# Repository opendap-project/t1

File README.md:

# t1

| Folder | Content |
| --- | --- |
| [`board/`](board/README.md) | Main board of the OpenDAP T1: the SoC-based single board computer, its auxiliary MCUs and simulations |
| [`case/`](case/README.md) | The physical case of the OpenDAP T1: the core with its basic back cover, the device-side HAT case mechanics, and the mount that faceplates attach to |
| [`faceplates/cassette/`](faceplates/cassette/README.md) | Cassette faceplate, inspired by cassette Walkmans |
| [`faceplates/classic/`](faceplates/classic/README.md) | Classic faceplate, inspired by classic portable music players |
| [`faceplates/touch/`](faceplates/touch/README.md) | Touch faceplate, the default faceplate: touch display, status LED, microphone |
| [`product/`](product/README.md) | Product integration of the OpenDAP T1: product requirements, the complete assembly and system simulations, built from the exports of every component |

Each folder keeps its own `README.md`, `CLAUDE.md` and `REUSE.toml`; the licence texts are in `LICENSES/`. The folders came from the former `board`, `case`, `faceplate-cassette`, `faceplate-classic`, `faceplate-touch` and `t1` repositories with their history ([RFC 0017](https://github.com/opendap-project/rfcs/blob/main/text/0017-naming-and-topology.md)).

## License

This repository follows the [REUSE](https://reuse.software) layout: licence texts in `LICENSES/`, and each folder's `REUSE.toml` maps its paths. Copyright © 2026 The OpenDAP Project.

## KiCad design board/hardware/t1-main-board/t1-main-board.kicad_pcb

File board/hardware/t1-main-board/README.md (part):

# T1 main board project

The KiCad 10 project of the T1 main board. The schematic is captured block by block ([feature-block catalog](../../docs/specs/feature-blocks.md), [RFC 0011](https://github.com/opendap-project/rfcs/blob/main/text/0011-feature-blocks-and-variants.md)); the board is at its placement stage: every part placed, nothing routed ([placement v1](../../docs/specs/placement-v1.md)). Prototype 1 targets quality level Q1 ([RFC 0010](https://github.com/opendap-project/rfcs/blob/main/text/0010-quality-levels.md)).

The schematic is generated: `generator/` writes every sheet, the project file, the library tables and the project-local library parts from the board's data. Edit the generator and run it again; never edit a generated file by hand. A rerun with no change in its inputs writes byte-identical files (every UUID is derived from a stable key).

## Layout

| Path | What it is |
|---|---|
| `t1-main-board.kicad_pro` | The project: drawing sheet, text variables, ERC severities (CRAFT-158), net classes and their patterns. Generated |
| `t1-main-board.kicad_sch` | The root sheet: the block diagram. Generated |
| `power.kicad_sch`, `interconnect.kicad_sch` | The power and interconnect overviews. Generated |
| `<block>.kicad_sch` | One sheet per feature block, named after its ID without `blk.` (CRAFT-82). Generated |
| `sym-lib-table`, `fp-lib-table` | Library tables: libs `kicad/` through `${KIPRJMOD}/../lib/opendap`, the project library through `${KIPRJMOD}/../lib`, KiCad's stock libraries through `${KICAD10_SYMBOL_DIR}` and `${KICAD10_FOOTPRINT_DIR}`. Generated |
| `t1-main-board.kicad_pcb` | The board: outline, holes, stackup v3, rule areas, fiducials and every part placed; not routed. Generated by `pcb/` |
| `t1-main-board.dru.toml`, `t1-main-board.kicad_dru` | The rule sources and the composed rules ([`../rules/`](../rules/)) |
| `shields.toml` | The shield-can frames (`blk.shields`): the inside area of each frame, land, keep-outs, lid and height; the generator draws the frame lands from it and the placement reserves them (both through `pcb/shields.py`). By hand |
| `t1-main-board.craft.toml` | The craft check configuration: target level and mirrored blocks (CRAFT-34) by hand; its `[schematic]` table (rails and each block's interface, CRAFT-85, -112) generated below the marker line |
| `generator/` | The generator (Python 3.11 or later, no other dependency); `parts.area_swap` applies the area swaps of BOM v1.16 and v1.17 to every placed part |
| `pcb/` | The placement tool (Python 3.11 or later and KiCad 10's Python): `build.py` writes the board from the schematic; `plan.py` holds the placement plan and its decisions; `proximity.py` checks that every converter's and IC's capacitors stand within a bound of the pins they serve (the build fails otherwise, placement v1 decision 14); `shields.py` derives the shield frames from `../shields.toml`; `fabref.py` centres each fabrication reference in its courtyard and sizes it to fit (the writer stops on an overlap); `plan.model_for` gives the KiCad stock lands whose KiCad 10 library ships no model (Littelfuse NANO2, TI DPY0002A, SOT-523, the XxL4020 land by part height) a libs `kicad/` envelope model; `variants.py` copies the schematic's KiCad 10 design-variant data onto the footprints (the `production` population for `--variant` fab outputs); `placement-result.json` is its report (area budget, occupancy, checks, capacitor proximity, shield frames, DRC summary). Tests: `python3 -m unittest discover hardware/t1-main-board/pcb/tests`; `tests/kicad_transform_check.py` (KiCad's Python) checks the footprint transform against pcbnew |
| `../lib/symbols/T1_Main_Board.kicad_sym`, `../lib/footprints/T1_Main_Board.pretty/` | Project-only parts libs `kicad/` does not carry yet: the TPS7A1006PDSER and shield-frame symbols, the Murata DFE252012F, DFE201610E, Abracon AOTA-B201610, Coilcraft XFL3012, C&K PTS815 and Vishay WSL (doc 30100 pad table, by model and resistance range) lands, the 0.8 mm test pad (PCB-D-06) and the shield-frame lands. Generated; each land carries its libs `kicad/` envelope model (libs v0.3.3) |

## Blocks captured

Drawn from 2026-10-25. Every sheet carries the block's notes (function, absent state, constraint IDs, ADRs), an interface table and a rail table.

| Page | Sheet | Block | Content |
|---|---|---|---|
| 1 | `t1-main-board.kicad_sch` | root | Block diagram in reading rows; the LPDDR4X and eMMC buses wired pin for pin |
| 2 | `power.kicad_sch` | power | Rail table of the drawn blocks and the power tree (power tree v0.11) |
| 3 | `interconnect.kicad_sch` | interconnect | Connector list; pin maps come with the connector blocks |
| 4-7 | `charger*.kicad_sch` | `blk.charger`, `-input`, `-core`, `-battery` | TPS2121 input mux and OV interlocks; BQ25798 2S charger; CSD17575Q3 ship FET, 5 A fuse, BATP and the six battery contacts with ESD (board ADRs 0014, 0020) |
| 8 | `gauge.kicad_sch` | `blk.gauge` | BQ28Z610-R1 on the pack side, 3 mΩ low-side sense, board NTC (board ADR 0017) |
| 9 | `pwr-vsys-lv.kicad_sch` | `blk.pwr-vsys-lv` | TPS62136, VSYS to VSYS_LV 3.8 V |
| 10 | `pwr-3v3-sys.kicad_sch` | `blk.pwr-3v3-sys` | TPS62827, vcc3v3_sys 3.3 V |
| 11 | `pmic.kicad_sch` | `blk.pmic` | RK809-5: bucks, LDOs, RTC, control |
| 12 | `vdd-cpu.kicad_sch` | `blk.vdd-cpu` | TPS62870Z4 vdd_cpu with differential sense and compensation (board ADR 0026) |
| 13-20 | `soc*.kicad_sch` | `blk.soc`, `blk.soc-*` | RK3566 by IO domain: PMU IO with clock, reset and pull-ups; DDR; VCCIO1-4; VCCIO5-7; the PHYs (USB 2.0 and 3, multi-PHY, CSI RX, DSI, HDMI, eDP); supplies; ground |
| 21 | `lpddr4x.kicad_sch` | `blk.lpddr4x` | Micron MT53E1G32D2FW-046 (board ADR 0022), TPS7A1006 VDDQ, links |
| 22-33 | `audio*.kicad_sch`, `mclk`, `dac-*`, `hpa-*` | `blk.audio` and its sub-sheets | DAC supplies, divided master clocks (ADR 0019), two CS43198, ±7 V and ±6 V rails, six OPA1622 |
| 34 | `jack-se.kicad_sch` | `blk.jack-se` | The 3.5 mm jack |
| 35-37 | `rp2354*.kicad_sch` | `blk.rp2354`, `-core`, `-power` | RP2354A (one reference, three units): system and GPIO units with the 12 MHz oscillator, BOOTSEL N-FET, 27 Ω USB series, the five I2S/DSD tap positions and test pads; the supply unit with its 3.3 µH core regulator, RP_3V3 and RP_IOVDD_1V8 switches, links #21 and #30 |
| 38 | `emmc.kicad_sch` | `blk.emmc` | Samsung KLMBG2JETD-B041 eMMC, 16 GB alternate |
| 39 | `mic-ambient.kicad_sch` | `blk.mic-ambient` | IM73D122 on PDM CLK1 and SDI1, 22 Ω clock series, link #35 from MIC_1V8 |
| 40 | `jack-bal.kicad_sch` | `blk.jack-bal` | The 4.4 mm jack |
| 41 | `maskrom.kicad_sch` | `blk.maskrom` | TPS3808G01 boot window (WINDOW_N), SN74LVC1G57 and SN74LVC1G58 on vcca1v8_pmu, BAT54 from PWRON_N, DMG1012T pulling EMMC_D0 through 1 kΩ |
| 42 | `current-monitors.kicad_sch` | `blk.current-monitors` | Five INA236 on I2C1 (0x40, 0x41, 0x43; INA236B at 0x48, 0x49) and their shunts on Vishay's WSL lands: VSYS 10 mΩ, audio VSYS_LV and VSYS sides 20 mΩ each, display 100 mΩ, HAT 20 mΩ |
| 43 | `debug.kicad_sch` | `blk.debug` | Debug UART2 and I2S/DSD pads with ground, reset and PMIC pads, the spare SoC GPIO pads (the `DEBUG` bus), a pad on every rail no other sheet probes |
| 44 | `pwr-5v1.kicad_sch` | `blk.pwr-5v1` | TPS62903 5.1 V source, enabled by either port (OR of HAT5V_EN, USB_SRC_ON) |
| 45 | `usb-vbus-out.kicad_sch` | `blk.usb-vbus-out` | eFuse #D (shared limiter) and eFuse #C (USB-C source), TPS259470A (RFC 0015) |
| 46 | `usb-c.kicad_sch` | `blk.usb-c` | USB4105 receptacle, TVS2200, TPD8S300A, TPD4E05U06, FUSB302B, VBUSDET divider |
| 47 | `hat-signals.kicad_sch` | `blk.hat-signals` | DF40C-50DS flat-cable receptacle (interface v2 §9.2), USB 3 TX AC coupling |
| 48 | `hat-5v.kicad_sch` | `blk.hat-5v` | eFuse #A, FUSB302B01 (USB PD on the HAT port), VBUS discharge (RFC 0014) |
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
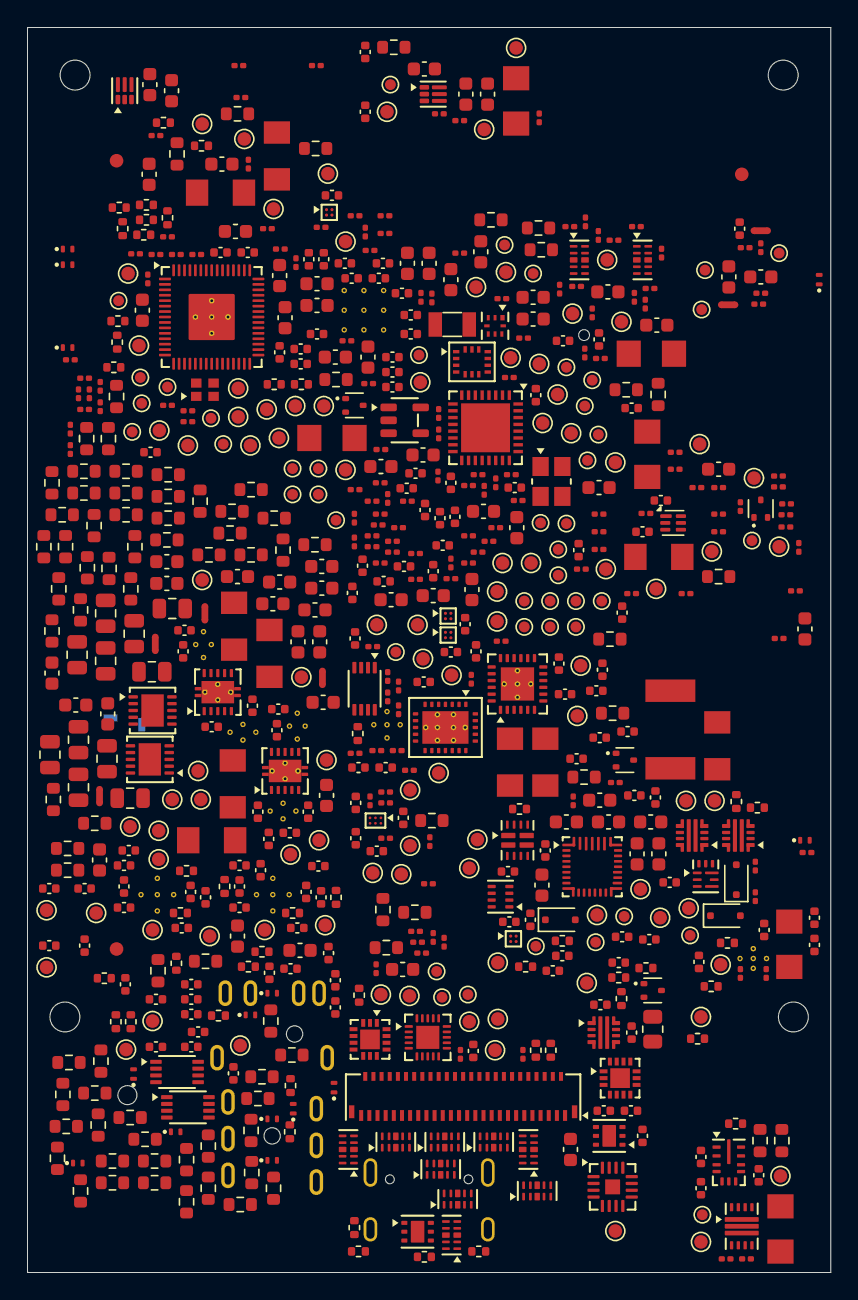
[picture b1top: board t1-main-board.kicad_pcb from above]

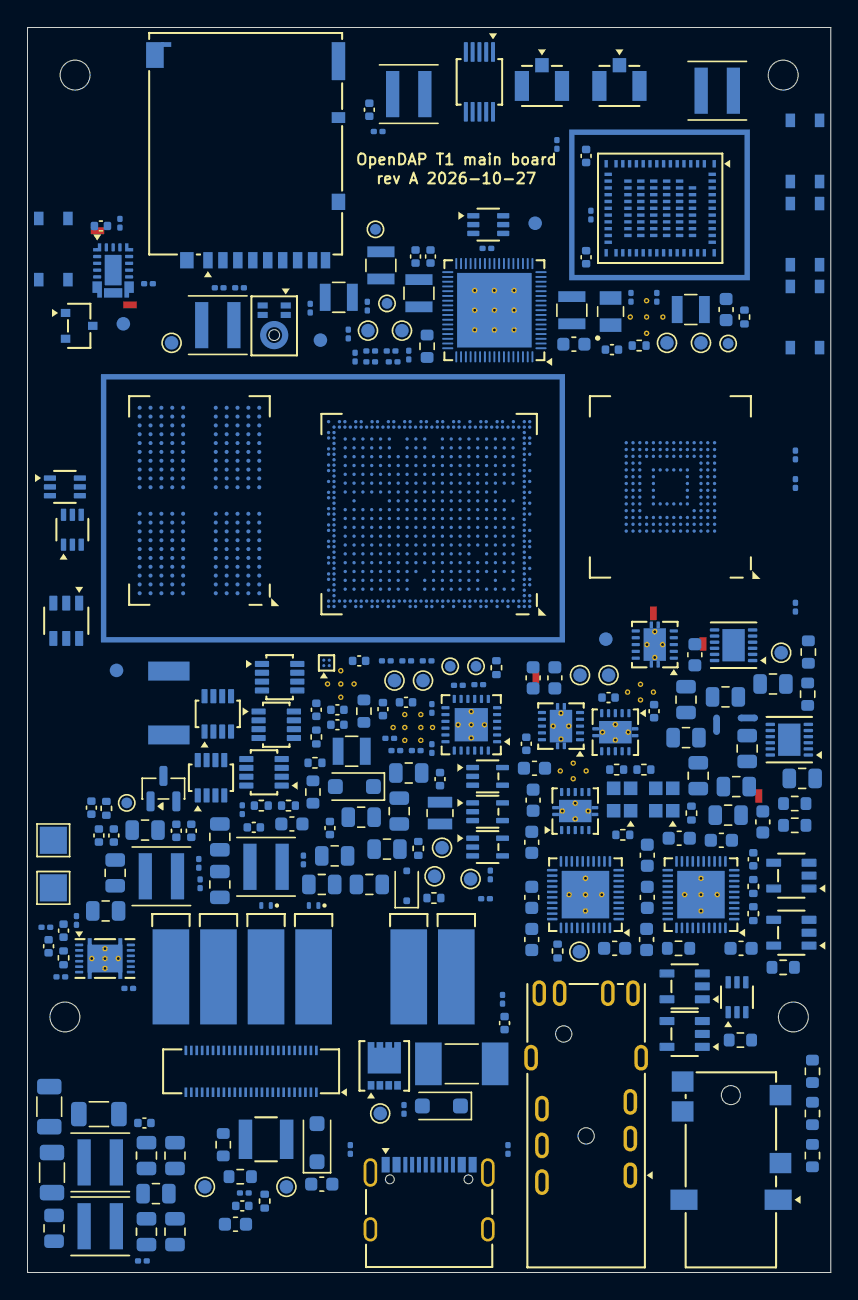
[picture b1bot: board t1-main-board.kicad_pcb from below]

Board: 6 copper layers, 59.1 x 91.6 mm, 1008 parts (279 on the bottom side), 600 nets, no tracks yet.

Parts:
A5901: Shield_Frame_SOC; Shield_Frame_SOC_34.15x19.75mm
A5902: Shield_Frame_RADIO; Shield_Frame_RADIO_13.3x11.1mm
C501, C607, C611, C617, C801, C804, C805, C806, C2401, C2408, C2409, C2503, C2504, C2506, C2603, C2604, C2606, C2804, C2812, C3005, C3006, C3011, C3012, C3205, C3206, C3211, C3212, C3305, C3306, C3311, C3312, C3902, C4201, C4202, C4203, C4204, C4205, C4805, C5502: 100 nF; C_0402_1005Metric
C502, C503, C802, C1110, C1111, C1112, C1113, C1122, C1123, C1124, C1125, C1126, C1127, C1128, C1129, C1130, C1131, C1132, C1133, C1134, C1135, C1335, C1337, C2111, C2301, C2302, C2813, C3516, C3517, C3901, C4501, C4502, C4503, C4504, C4602, C4603, C4801, C4802, C4804, C5103, C5301, C5302, C5303, C5701, C6001, C6002, C6501, C6601, C6602, C6801, C6802: 1 µF; C_0402_1005Metric
C601, C1001, C2507, C2607, C5401: 4.7 µF; C_0603_1608Metric
C602, C603, C604: 47 nF; C_0402_1005Metric
C605, C606, C612, C613, C614, C615, C616, C1004, C1101, C1103, C1106, C1108, C1116, C1117, C1118, C1119, C1120, C1121, C1328, C5001, C5002, C5003, C5104, C5501, C6201: 10 µF; C_0603_1608Metric
C608, C609, C610, C618, C619, C2814, C2815: 10 µF; C_0805_2012Metric
C803, C2402, C2403, C2404, C2405, C2501, C2502, C2505, C2508, C2510, C2512, C2513, C2514, C2515, C2516, C2601, C2602, C2605, C2608, C2610, C2612, C2613, C2614, C2615, C2616, C3801: 2.2 µF; C_0402_1005Metric
C901, C903, C904, C2902, C2903, C2904, C2906, C2907, C2908, C2911, C2912, C2913, C2914, C2915, C2916, C2917, C2918, C2919, C2920, C2921, C2922, C4402, C4403, C4404: 22 µF; C_0805_2012Metric
C902: 3.3 nF; C_0402_1005Metric
C1002, C5106: 120 pF; C_0402_1005Metric
C1003, C1102, C1104, C1105, C1107, C1109, C1208, C1311, C1312, C1313, C1318, C1321, C1323, C2112, C2113, C5105: 22 µF; C_0603_1608Metric
C1114, C1115, C1202, C1204, C1205, C1303, C1308, C1314, C1319, C1322, C1324, C1325, C1326, C1329, C1330, C1331, C1334, C1336, C1338, C1339, C1340, C1341, C1342, C1343, C1344, C1345, C1346, C1347, C1348, C1349, C2101, C2102, C2103, C2104, C2105, C2106, C2107, C2108, C2109, C2110, C2115, C3501, C3502, C3503, C3504, C3505, C3506, C3507, C3509, C3510, C3511, C3513, C3514, C4101, C4103, C4104, C4604, C4701, C4702, C5004, C5101, C5102, C5601, C5702, C5703, C5704, C6202, C6301, C6302, C6401, C6701, C6702: 100 nF; C_0201_0603Metric
C1201, C1203: 47 µF; C_0603_1608Metric
C1206: 5.6 nF; C_0402_1005Metric
C1207, C2811: 22 pF; C_0402_1005Metric
C1301, C1302: 10 pF; C_0402_1005Metric
C1304, C1305, C1306, C1307, C4505, C4803: 1 nF; C_0402_1005Metric
C1309, C1310, C1315, C1316, C1317, C1320, C1327, C1332, C1333, C2114, C2116, C2303, C2805, C2806, C3508, C3512, C3515: 4.7 µF; C_0402_1005Metric
C2304: 10 µF; C_0402_1005Metric
C2406, C2407, C2802, C4401: 10 nF; C_0402_1005Metric
C2509, C2511, C2609, C2611: 15 µF; C_0603_1608Metric
C2801: 15 pF; C_0402_1005Metric
C2803, C5402: 220 nF; C_0402_1005Metric
C2807, C2808, C2809, C2810, C2816, C2901, C2905: 4.7 µF; C_0805_2012Metric
C2817, C2818, C2819: 22 µF; C_1206_3216Metric
C2909, C2910, C2923, C2924: 470 nF; C_0603_1608Metric
C3001, C3002, C3003, C3004, C3007, C3008, C3009, C3010, C3201, C3202, C3203, C3204, C3207, C3208, C3209, C3210, C3301, C3302, C3303, C3304, C3307, C3308, C3309, C3310: 100 pF; C_0603_1608Metric
C4102: 390 nF; C_0603_1608Metric
C4601: 100 nF; C_0603_1608Metric
C5201, C5202, C5203, C5204: DNP; C_0201_0603Metric
C5205: 10 pF; C_0201_0603Metric
C5304, C6502: 1 µF; C_0201_0603Metric
C5403: 1 µF; C_0603_1608Metric
C6603, C6604: 470 nF; C_0402_1005Metric
D501, D502, D4401, D4402: BAT54J; D_SOD-323F
D701: TVS; D_SOD-123F
D702, D703, D3401, D3402, D3403, D4001, D4002, D4003, D4004, D4005, D5301, D5801, D6901, D6902, D6903, D6904: TPD1E10B06; Texas_DPY0002A_0.6x1mm_P0.65mm
D2801: PMEG2010AEH; D_SOD-123F
D4101: BAT54; Nexperia_SOT23_TO-236AB_2.9x1.3mm_P1.9mm
D5401: PMEG6010CEH; D_SOD-123F
F701: 5 A; Fuse_Littelfuse-NANO2-451_453
FID1, FID2, FID3, FID4, FID5, FID6, FID7, FID8: Fiducial; Fiducial_1mm_Mask2mm
H1, H2, H3, H4: MountingHole_2.2mm
J701, J702, J703, J704, J705, J706: 70-9258-001-120-006; KYOCERA_AVX_9258-100_70-9258-001-120-006_SpringFinger_Pad7.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
J3401: SJ2-35954D-SMT-TR; Same_Sky_SJ2-35954D-SMT-TR_Jack_3.5mm_TRRS_Horizontal
J4001: GT-3321667P-01; G_Switch_GT-3321667P-01_Jack_4.4mm_5Pole_Horizontal
J4601: USB4105-GF-A; GCT_USB4105-GF-A_USB-C_Receptacle_USB2.0_Horizontal
J4701: DF40C-50DS-0.4V(51); Hirose_DF40C-50DS-0.4V_2x25_P0.4mm_Vertical
J5201, J5202: U.FL-R-SMT-1; Hirose_U.FL-R-SMT-1_Vertical
J5301: FH35C-51S-0.3SHW; Hirose_FH35C-51S-0.3SHW_1x51-1MP_P0.3mm_Horizontal
J6201: DM3AT-SF-PEJM5; Hirose_DM3AT-SF-PEJM5_microSD_PushPush_Top
L601, L4401: 1 µH; L_Coilcraft_XxL4020
L901: 1.5 µH; L_Coilcraft_XxL4020
L1001, L5101: 470 nH; L_Coilcraft_XxL4020
L1101, L1102, L1103, L1104, L1105: 470 nH; L_Murata_DFE252012F
L1201: 92 nH; L_Coilcraft_XxL4020
L2301: 2.2 µH; L_Murata_DFE201610E
L2801: 4.7 µH; L_Murata_DFE252012F
L2802: 2.2 µH; L_Coilcraft_XxL4020
L3501: 3.3 µH; L_Abracon_AOTA-B201610
L5401: 22 µH; L_Coilcraft_XFL3012
MK3901: IM73D122V01XTMA1; Infineon_PG-LLGA-5-3_3x4mm_P0.7mm_BottomPort
NT1201, NT1202, NT3401, NT3402: NetTie; NetTie-2_SMD_Pad0.5mm
NT2901, NT2902, NT2903, NT2904: 20 mΩ trace; NetTie-2_SMD_Pad0.5mm
Q701: CSD17575Q3; Texas_Q3_SON-8_3.3x3.3mm_P0.65mm
Q2801, Q3501, Q4101, Q4801: DMG1012T; SOT-523
Q2802: DMP3099L; SOT-23
R501: 1.02 MΩ; R_0402_1005Metric
R502, R504, R2407, R2408, R2409, R2410, R2806, R2807, R2808, R4804: 100 kΩ; R_0402_1005Metric
R503: 464 kΩ; R_0402_1005Metric
R505: 31.6 kΩ; R_0402_1005Metric
R506, R4503, R4601, R4604, R4802: 10 kΩ; R_0402_1005Metric
R507: 45.3 kΩ; R_0402_1005Metric
R601: 6.04 kΩ; R_0201_0603Metric
R602, R605, R1303, R1304, R1312, R1319, R3802, R3803, R3804, R5305, R5306, R6001, R6105, R6106, R6501, R6701, R6705, R6706, R6707, R6708, R6709: 10 kΩ; R_0201_0603Metric
R603: 5.23 kΩ; R_0201_0603Metric
R604: 30.1 kΩ; R_0201_0603Metric
R701, R801, R804, R805, R806, R807, R6207: 100 Ω; R_0201_0603Metric
R802: 5.1 Ω; R_0402_1005Metric
R803: 10 Ω; R_0201_0603Metric
R808: 3 mΩ; R_Vishay_WSL1206_2m-5m9
R901: 442 kΩ; R_0201_0603Metric
R902, R1002, R1003, R1103, R1204, R1327, R1328, R1329, R1330, R1331, R1332, R1333, R1334, R1335, R1336, R4101, R4103, R4104, R4105, R4403, R5101, R5102, R5103, R5108, R5302, R5307, R5308, R5501, R5801, R6702, R6703, R6704, R6901: 100 kΩ; R_0201_0603Metric
R903: 470 kΩ; R_0201_0603Metric
R904, R1004, R1203, R1339, R2102: 5 mΩ; R_Vishay_WSL1206_2m-5m9
R1001: 453 kΩ; R_0201_0603Metric
R1101: 47 kΩ; R_0201_0603Metric
R1102: 120 kΩ; R_0201_0603Metric
R1104: 22 kΩ; R_0201_0603Metric
R1201: 51 kΩ; R_0201_0603Metric
R1202: 82.5 Ω; R_0201_0603Metric
R1301: 1 MΩ; R_0201_0603Metric
R1302, R3801, R3902, R6201, R6202, R6203, R6204, R6205, R6206, R6502: 22 Ω; R_0201_0603Metric
R1305, R1306, R1307, R1308, R1309, R1310, R5701, R6101, R6102: 2.2 kΩ; R_0201_0603Metric
R1311, R1313, R1314, R1315, R1316, R1317, R1318, R1321, R1322, R1324, R1326, R3501, R6103, R6104: 4.7 kΩ; R_0201_0603Metric
R1320: 120 Ω; R_0201_0603Metric
R1323, R1325, R1337, R1338, R2403, R2405, R2501, R2504, R2505, R2601, R2602, R2603, R2604, R2605, R3504, R3505, R3506, R3507, R3508, R5001, R5002, R5003, R5004, R5005, R5006, R5107, R5109, R5503: 0 Ω; R_0402_1005Metric
R1340: 0 Ω; R_0603_1608Metric
R2101: 240 Ω; R_0201_0603Metric
R2103, R3021, R3022, R3101, R3102, R4202, R4205, R5104, R5111: 20 mΩ; R_Vishay_WSL1206_6m-200m
R2104, R3511, R3805, R3806, R5303, R5502, R5702, R6002, R6208, R6601, R6801: 100 mΩ; R_0603_1608Metric
R2301, R2303, R2401, R2402, R2506, R2607, R3009, R3010, R3019, R3020, R3209, R3210, R3219, R3220, R3309, R3310, R3319, R3320, R3512, R5304: 1 Ω; R_0603_1608Metric
R2302: 4.32 kΩ; R_0402_1005Metric
R2404, R2406: 33 Ω; R_0402_1005Metric
R2411, R2412: 27 Ω; R_0402_1005Metric
R2502, R2503: 22 Ω; R_0402_1005Metric
R2606: 4.99 kΩ; R_0402_1005Metric
R2801: 100 Ω; R_0402_1005Metric
R2802: 475 kΩ; R_0603_1608Metric
R2803, R2805, R5106: 100 kΩ; R_0603_1608Metric
R2804: 16.5 kΩ; R_0603_1608Metric
R2901, R2902: 523 Ω; R_0603_1608Metric
R2903, R2904, R2907, R2908: 60.4 kΩ; R_0603_1608Metric
R2905, R2906: 13 kΩ; R_0603_1608Metric
R3001, R3003, R3005, R3007, R3011, R3013, R3015, R3017, R3201, R3203, R3205, R3207, R3211, R3213, R3215, R3217, R3301, R3303, R3305, R3307, R3311, R3313, R3315, R3317, R5110: 1 kΩ; R_0603_1608Metric
R3002, R3004, R3006, R3008, R3012, R3014, R3016, R3018, R3202, R3204, R3206, R3208, R3212, R3214, R3216, R3218, R3302, R3304, R3306, R3308, R3312, R3314, R3316, R3318: 1.62 kΩ; R_0603_1608Metric
R3502, R3503: 27 Ω; R_0201_0603Metric
R3509, R4106: 1 kΩ; R_0201_0603Metric
R3510: 33 Ω; R_0201_0603Metric
R3901, R6301, R6401, R6503: 10 Ω; R_0603_1608Metric
R4102: 280 kΩ; R_0201_0603Metric
R4201: 10 mΩ; R_Vishay_WSL2512_7m-500m
R4203: 100 mΩ; R_Vishay_WSL1206_6m-200m
R4204: 20 mΩ; R_Vishay_WSL2010_7m-500m
R4401: 95.3 kΩ; R_0201_0603Metric
R4402: 26.1 kΩ; R_0201_0603Metric
R4501: 1.47 kΩ; R_0402_1005Metric
R4502, R4801: 1.87 kΩ; R_0402_1005Metric
R4602, R4603, R4701, R4702: 2.2 Ω; R_0402_1005Metric
R4605: 15 kΩ; R_0402_1005Metric
R4803: 100 Ω; R_0805_2012Metric
R5105: 200 kΩ; R_0603_1608Metric
R5201, R5202: 0 Ω; R_0201_0603Metric
R5301: 3.57 kΩ; R_0201_0603Metric
R5401: 3.32 Ω; R_0603_1608Metric
RT801: 10 kΩ; R_0402_1005Metric
SW6901, SW6902, SW6903: PTS815; SW_CK_PTS815
SW6904: PTS815 400 gf; SW_CK_PTS815
TP501: USBC_VBUS; TestPoint_Pad_D1.0mm
TP502: HAT_5V; TestPoint_Pad_D1.0mm
TP503: VBUS_CHG; TestPoint_Pad_D1.0mm
TP504: MUX_ST; TestPoint_Pad_D0.8mm
TP601: VSYS; TestPoint_Pad_D1.0mm
TP602: CHG_STAT; TestPoint_Pad_D0.8mm
TP603: CHG_QON; TestPoint_Pad_D0.8mm
TP701: VBAT; TestPoint_Pad_D1.0mm
TP702: BAT_P; TestPoint_Pad_D1.0mm
TP901: VSYS_LV_PG; TestPoint_Pad_D0.8mm
TP902: VSYS_LV_SRC; TestPoint_Pad_D1.0mm
TP903, TP5501, TP6601: VSYS_LV; TestPoint_Pad_D1.0mm
TP1001: VCC3V3_SYS_PG; TestPoint_Pad_D0.8mm
TP1002: VCC3V3_SYS_SRC; TestPoint_Pad_D1.0mm
TP1003, TP3801, TP6801: vcc3v3_sys; TestPoint_Pad_D1.0mm
TP1101: PMIC_BATDIV; TestPoint_Pad_D0.8mm
TP1102: PMIC_SNS; TestPoint_Pad_D0.8mm
TP1201: VDD_CPU_SRC; TestPoint_Pad_D1.0mm
TP1202: vdd_cpu; TestPoint_Pad_D1.0mm
TP1203: VDD_CPU_PG; TestPoint_Pad_D0.8mm
TP1204: VDD_CPU_VOS; TestPoint_Pad_D0.8mm
TP1301: VDD_LOGIC_SRC; TestPoint_Pad_D1.0mm
TP1302: vdd_logic; TestPoint_Pad_D1.0mm
TP2101: VCC_DDR_SRC; TestPoint_Pad_D1.0mm
TP2102: vcc_ddr; TestPoint_Pad_D1.0mm
TP2103: VCC0V6_DDR_SRC; TestPoint_Pad_D1.0mm
TP2104: vcc0v6_ddr; TestPoint_Pad_D1.0mm
TP2105, TP5701, TP6301, TP6401: vcca1v8_pmu; TestPoint_Pad_D1.0mm
TP2106: vcc1v8_ddr; TestPoint_Pad_D1.0mm
TP2301: DAC_DIG_1V8_SRC; TestPoint_Pad_D1.0mm
TP2302: DAC_DIG_1V8; TestPoint_Pad_D1.0mm
TP2303: AUDIO_2V2_SRC; TestPoint_Pad_D1.0mm
TP2304, TP2403, TP2501, TP2601: AUDIO_2V2; TestPoint_Pad_D1.0mm
TP2401: VSYS_LV_AUDIO; TestPoint_Pad_D1.0mm
TP2402: MCLK3V1_IN; TestPoint_Pad_D1.0mm
TP2404: MCLK1V8_IN; TestPoint_Pad_D1.0mm
TP2502: DACL_VA_IN; TestPoint_Pad_D1.0mm
TP2503: MCLK_L; TestPoint_Pad_D1.0mm
TP2602: DACR_VA_IN; TestPoint_Pad_D1.0mm
TP2603: MCLK_R; TestPoint_Pad_D1.0mm
TP3001, TP3101: HPA_P6V0; TestPoint_Pad_D1.0mm
TP3002: HPA_P6V0_SE; TestPoint_Pad_D1.0mm
TP3003, TP3103: HPA_N6V0; TestPoint_Pad_D1.0mm
TP3004: HPA_N6V0_SE; TestPoint_Pad_D1.0mm
TP3102: HPA_P6V0_BAL; TestPoint_Pad_D1.0mm
TP3104: HPA_N6V0_BAL; TestPoint_Pad_D1.0mm
TP3501: RP_SWCLK; TestPoint_Pad_D0.8mm
TP3502: RP_SWDIO; TestPoint_Pad_D0.8mm
TP3503: RP_RUN; TestPoint_Pad_D0.8mm
TP3504: RP_QSPI_SS; TestPoint_Pad_D0.8mm
TP3505: RP_SPARE; TestPoint_Pad_D0.8mm
TP3506: RP_3V3_SRC; TestPoint_Pad_D1.0mm
TP3507: RP_3V3; TestPoint_Pad_D1.0mm
TP3508: RP_IOVDD_1V8_SRC; TestPoint_Pad_D1.0mm
TP3509: RP_IOVDD_1V8; TestPoint_Pad_D1.0mm
TP3802: EMMC_VCC; TestPoint_Pad_D1.0mm
TP3803: vcc_1v8; TestPoint_Pad_D1.0mm
TP3804: EMMC_VCCQ; TestPoint_Pad_D1.0mm
TP3901, TP6501, TP6503: MIC_1V8; TestPoint_Pad_D1.0mm
TP3902: MIC_AMB_VDD; TestPoint_Pad_D1.0mm
TP4101: WINDOW_N; TestPoint_Pad_D0.8mm
TP4301: DBG_UART_TX; TestPoint_Pad_D0.8mm
TP4302: DBG_UART_RX; TestPoint_Pad_D0.8mm
TP4303, TP4309: GND; TestPoint_Pad_D1.0mm
TP4304: I2S_BCLK; TestPoint_Pad_D0.8mm
TP4305: I2S_LRCK; TestPoint_Pad_D0.8mm
TP4306: I2S_SDO0; TestPoint_Pad_D0.8mm
TP4307: DSD_L; TestPoint_Pad_D0.8mm
TP4308: DSD_R; TestPoint_Pad_D0.8mm
TP4310: SOC_RESET_N; TestPoint_Pad_D0.8mm
TP4311: PMIC_INT_N; TestPoint_Pad_D0.8mm
TP4312: PMIC_SLEEP; TestPoint_Pad_D0.8mm
TP4313: PWRON_N; TestPoint_Pad_D0.8mm
TP4314: SPARE_1A0; TestPoint_Pad_D0.8mm
TP4315: SPARE_1A1; TestPoint_Pad_D0.8mm
TP4316: SPARE_1A3; TestPoint_Pad_D0.8mm
TP4317: SPARE_1A4; TestPoint_Pad_D0.8mm
TP4318: SPARE_1A5; TestPoint_Pad_D0.8mm
TP4319: SPARE_1A6; TestPoint_Pad_D0.8mm
TP4320: SPARE_1A7; TestPoint_Pad_D0.8mm
TP4321: SPARE_1B3; TestPoint_Pad_D0.8mm
TP4322: SPARE_1D0; TestPoint_Pad_D0.8mm
TP4323: SPARE_1D1; TestPoint_Pad_D0.8mm
TP4324: SPARE_1D3; TestPoint_Pad_D0.8mm
TP4325: SPARE_2B1; TestPoint_Pad_D0.8mm
TP4326: SPARE_2B2; TestPoint_Pad_D0.8mm
TP4327: SPARE_3B7; TestPoint_Pad_D0.8mm
TP4328: SPARE_3C0; TestPoint_Pad_D0.8mm
TP4329: SPARE_3C4; TestPoint_Pad_D0.8mm
TP4330: SPARE_3C5; TestPoint_Pad_D0.8mm
TP4331: SPARE_4C7; TestPoint_Pad_D0.8mm
TP4332: SPARE_4D0; TestPoint_Pad_D0.8mm
TP4333: SPARE_4D1; TestPoint_Pad_D0.8mm
TP4334: vdd_gpu; TestPoint_Pad_D1.0mm
TP4335: vdd_npu; TestPoint_Pad_D1.0mm
TP4336: vccio6_1v8; TestPoint_Pad_D1.0mm
TP4337: vdda0v9_image; TestPoint_Pad_D1.0mm
TP4338: vdda_0v9; TestPoint_Pad_D1.0mm
TP4339: vdda0v9_pmu; TestPoint_Pad_D1.0mm
TP4340: vccio_sd; TestPoint_Pad_D1.0mm
TP4341: vcc3v3_pmu; TestPoint_Pad_D1.0mm
TP4342: vcca_1v8; TestPoint_Pad_D1.0mm
TP4343: vcca1v8_image; TestPoint_Pad_D1.0mm
TP4344: DAC_VP; TestPoint_Pad_D1.0mm
TP4345: DAC1_VA; TestPoint_Pad_D1.0mm
TP4346: DAC2_VA; TestPoint_Pad_D1.0mm
TP4347: MCLK_3V1; TestPoint_Pad_D1.0mm
TP4348: MCLK_1V8; TestPoint_Pad_D1.0mm
TP4349: AUDIO_P7V0; TestPoint_Pad_D1.0mm
TP4350: AUDIO_N7V0; TestPoint_Pad_D1.0mm
TP4351: BAT_N; TestPoint_Pad_D1.0mm
TP4352: FP_VCI_SRC; TestPoint_Pad_D1.0mm
TP4353: VSYS_SRC; TestPoint_Pad_D1.0mm
TP4354: VSYS_AUDIO; TestPoint_Pad_D1.0mm
TP4355: VSYS_LV_BL; TestPoint_Pad_D1.0mm
TP4356: VSYS_P5V1; TestPoint_Pad_D1.0mm
TP4401: P5V1_SRC; TestPoint_Pad_D1.0mm
TP4402: P5V1_PG; TestPoint_Pad_D0.8mm
TP4501: EFUSE_5V_IMON_ILM; TestPoint_Pad_D0.8mm
TP4601: USBC_SBU1; TestPoint_Pad_D0.8mm
TP4602: USBC_SBU2; TestPoint_Pad_D0.8mm
TP4603: USBC_PROT_FLT_N; TestPoint_Pad_D0.8mm
TP5101: WL_3V3_SRC; TestPoint_Pad_D1.0mm
TP5102: vcc3v3_wl; TestPoint_Pad_D1.0mm
TP5103: WL_1V8_SRC; TestPoint_Pad_D1.0mm
TP5104: vcc1v8_wl; TestPoint_Pad_D1.0mm
TP5301: FP_3V3_SRC; TestPoint_Pad_D1.0mm
TP5302: FP_3V3; TestPoint_Pad_D1.0mm
TP5303: FP_1V8_SRC; TestPoint_Pad_D1.0mm
TP5304: FP_1V8; TestPoint_Pad_D1.0mm
TP5502: SPK_VDD; TestPoint_Pad_D1.0mm
TP5503: SPK_P; TestPoint_Pad_D1.0mm
TP5504: SPK_N; TestPoint_Pad_D1.0mm
TP5702: TPM_VDD; TestPoint_Pad_D1.0mm
TP5801: COVER; TestPoint_Pad_2.0x2.0mm
TP5802: COVER_GND; TestPoint_Pad_2.0x2.0mm
TP6001: FP_VCI_OUT; TestPoint_Pad_D1.0mm
TP6002: FP_VCI; TestPoint_Pad_D1.0mm
TP6201: vcc3v3_sd; TestPoint_Pad_D1.0mm
TP6202: SD_VDD; TestPoint_Pad_D1.0mm
TP6302: IMU_VDD; TestPoint_Pad_D1.0mm
TP6402: NFC_TAG_VCC; TestPoint_Pad_D1.0mm
TP6403: NFC_TAG_LA; TestPoint_Pad_D1.0mm
TP6404: NFC_TAG_LB; TestPoint_Pad_D1.0mm
TP6502: MIC_1V8_FP; TestPoint_Pad_D1.0mm
TP6602: LED_VDD; TestPoint_Pad_D1.0mm
TP6802: HAPTIC_VDD; TestPoint_Pad_D1.0mm
TP6803: LRA_P; TestPoint_Pad_D1.0mm
TP6804: LRA_N; TestPoint_Pad_D1.0mm
U501: TPS2121RUXR; Texas_RUX0012A_VQFN-HR-12_2x2.5mm_P0.5mm
U601: BQ25798RQMR; VQFN-HR-29_4x4mm_P0.4mm
U801: BQ28Z610DRZR-R1; VSON-12-1EP_4x2.5mm_P0.4mm_EP2.45x1.95mm_ThermalVias
U901: TPS62136RGXR; Texas_RGX0011A_VQFN-HR-11_2x3mm_P0.5mm
U1001: TPS62827DMQR; Texas_DMQ0006A_VSON-HR-6_1.5x1.5mm_P0.5mm
U1101: RK809-5; QFN-68-1EP_7x7mm_P0.35mm_EP5.49x5.49mm_ThermalVias
U1201: TPS62870Z4WRXSR; Texas_RXS0016A_VQFN-FCRLF-16_2.55x3.55mm_P0.5mm
U1301: RK3566; Rockchip_FCCSP-565L_15.5x14.4mm_P0.4mm_P0.65mm_Ball0.25mm_P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
U1302: SN74LVC2G66DCUR; Texas_DCU0008A_VSSOP-8_2.3x2mm_P0.5mm
U2101: MT53E1G32D2FW-046; LPDDR4_FBGA-200_10.0x15.0mm_Layout12x22_P0.8x0.65mm_Pad0.3m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
U2102: TPS7A1006PDSER; WSON-6_1.5x1.5mm_P0.5mm
U2301, U2302, U3502, U3503, U5102: TPS22916CYFPR; Texas_YFP0004_DSBGA-4_0.78x0.78mm_Layout2x2_P0.4mm
U2303: TPS62840DLCR; Texas_DLC0008B_VSON-HR-8_1.5x2mm_P0.5mm
U2401, U4102: SN74LVC1G57DCKR; Texas_DCK0006A_SC-70-6_1.25x2mm_P0.65mm
U2402: TPS7A2031PDBVR; Texas_DBV0005A_SOT-23-5_1.6x2.9mm_P0.95mm
U2403, U2502, U2602: TPS7A2018PDBVR; Texas_DBV0005A_SOT-23-5_1.6x2.9mm_P0.95mm
U2404, U2405: SN74AUC1G74DCUR; Texas_DCU0008A_VSSOP-8_2.3x2mm_P0.5mm
U2501, U2601: CS43198-CNZR; QFN-40-1EP_5x5mm_P0.4mm_EP3.5x3.5mm_ThermalVias
U2801: TPS65131RGER; Texas_RGE0024B_VQFN-24-1EP_4x4mm_P0.5mm_EP2.45x2.45mm_Therm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
U2802: LMR33630CRNXR; Texas_RNX0012B_VQFN-HR-12_2x3mm_P0.5mm
U2901, U2902: LT3045EDD; Analog_DD_DFN-10-1EP_3x3mm_P0.5mm_EP1.65x2.38mm
U2903, U2904: LT3094EDD; Analog_DD_DFN-12-1EP_3x3mm_P0.45mm_EP1.65x2.38mm
U3001, U3002, U3201, U3202, U3301, U3302: OPA1622IDRCR; VSON-10-1EP_3x3mm_P0.5mm_EP1.65x2.4mm_ThermalVias
U3501: RP2354A; QFN-60-1EP_7x7mm_P0.4mm_EP3.4x3.4mm_ThermalVias
U3801: KLMBG2JETD-B041; Samsung_FBGA-153_11.5x13.0mm_Layout14x14_P0.5mm_Ball0.3mm_P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
U4101: TPS3808G01DBVR; Texas_DBV0006A_SOT-23-6_1.6x2.9mm_P0.95mm
U4103: SN74LVC1G58DCKR; Texas_DCK0006A_SC-70-6_1.25x2mm_P0.65mm
U4201, U4202, U4204: INA236AIDDFR; Texas_DDF0008A_SOT-23-8_1.6x2.9mm_P0.65mm
U4203, U4205: INA236BIDDFR; Texas_DDF0008A_SOT-23-8_1.6x2.9mm_P0.65mm
U4401: TPS62903RPJR; Texas_RPJ0009A_VQFN-HR-9_1.5x2mm_P0.5mm
U4501, U4502, U4801: TPS259470ARPWR; Texas_RPW0010A_VQFN-HR-10_2x2mm_P0.45mm
U4601: TVS2200DRVR; Texas_DRV0006A_WSON-6-1EP_2x2mm_P0.65mm_EP1x1.6mm
U4602: TPD8S300ARUKR; Texas_RUK0020B_WQFN-20-1EP_3x3mm_P0.4mm_EP1.7x1.7mm
U4603, U5301, U5302, U5303, U5304, U5305, U5306, U5307, U5308, U6201, U6202: TPD4E05U06DQAR; Texas_DQA0010A_USON-10_1x2.5mm_P0.5mm
U4604: FUSB302BMPX; onsemi_510BR_WQFN-14-1EP_2.5x2.5mm_P0.5mm_EP1.45x1.45mm
U4802: FUSB302B01MPX; onsemi_510BR_WQFN-14-1EP_2.5x2.5mm_P0.5mm_EP1.45x1.45mm
U5001: LBES5PL2EL-923; Murata_Type2EL_LGA-107_8.8x7.7mm
U5101: SN74AXC1T45DCKR; Texas_DCK0006A_SC-70-6_1.25x2mm_P0.65mm
U5103: TPS62826DMQR; Texas_DMQ0006A_VSON-HR-6_1.5x1.5mm_P0.5mm
U5309: TPS22950YBHR; Texas_YBH0006_DSBGA-6_0.706x1.106mm_Layout2x3_P0.4mm
U5310, U6001, U6501: TPS22945DCKR; Texas_DCK0005A_SC-70-5_1.25x2mm_P0.65mm
U5401: TPS61160DRVR; Texas_DRV0006A_WSON-6-1EP_2x2mm_P0.65mm_EP1x1.6mm
U5501: MAX98357AETE; Maxim_T1633-4_TQFN-16-1EP_3x3mm_P0.5mm_EP1.1x1.1mm
U5601: AT24C02D-STUM-T; Microchip_5TS1_SOT-23-5_1.6x2.9mm_P0.95mm
U5701: SLB9673XU20FW2613XTMA1; Infineon_PG-UQFN-32-1_5x5mm_P0.5mm_EP3.6x3.6mm
U6301: LSM6DSV16XTR; ST_LGA-14L_2.5x3mm_P0.5mm
U6401: NT3H2111W0FHKH; NXP_SOT902-3_XQFN-8_1.6x1.6mm_P0.5mm
U6601: LP5521YQX; Texas_NJA0024A_WQFN-24-1EP_4x5mm_P0.5mm_EP2.4x3.4mm_Thermal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
U6701: TCA6416ARTWR; Texas_RTW0024B_WQFN-24-1EP_4x4mm_P0.5mm_EP2.45x2.45mm_Therm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
U6801: DRV2605LDGSR; Texas_DGS0010A_VSSOP-10_3x3mm_P0.5mm
Y1101: 32.768 kHz; Crystal_SMD_3215-2Pin_3.2x1.5mm
Y1301: 24 MHz; Crystal_SMD_NDK_NX3225GA-4Pin_3.2x2.5mm
Y2401: 45.1584 MHz; Oscillator_SMD_NDK_NZ2520SDA-4Pin_2.5x2.0mm
Y2402: 49.152 MHz; Oscillator_SMD_NDK_NZ2520SDA-4Pin_2.5x2.0mm
Y3501: 12 MHz; Oscillator_SMD_ECS_ECS-2016MV-4Pin_2.0x1.6mm

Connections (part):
/3.3 V system rail/VCC3V3_SYS_PG: R1003.2, TP1001.1, U1001.2
/3.3 V system rail/VCC3V3_SYS_SW: L1001.1, U1001.5
/3.8 V pre-regulator/VSYS_LV_PG: R903.2, TP901.1, U901.7
/3.8 V pre-regulator/VSYS_LV_SW: L901.1, U901.2
/5.1 V source/P5V1_EN: D4401.1, D4402.1, R4403.1, U4401.5
/5.1 V source/P5V1_MODE: R4402.1, U4401.7
/5.1 V source/P5V1_PG: TP4402.1, U4401.1
/5.1 V source/P5V1_SS: C4401.1, U4401.8
/5.1 V source/P5V1_SW: L4401.1, U4401.2
/5.1 V source/P5V1_VSET: R4401.1, U4401.9
/ACTION_BTN_N: D6904.2, R1313.2, SW6904.1, U1301.AM37
/AUDIO_LN_EN: R1330.1, U1301.AF1, U2303.4, U2401.1, U2502.3, U2602.3
/Ambient microphone/MIC_AMB_CLK: MK3901.3, R3902.2
/Ambient microphone/MIC_AMB_VDD: C3901.1, C3902.1, MK3901.2, R3901.2, TP3902.1
/Antenna feeds/WL_ANT0_J: C5202.1, J5201.1, R5201.2
/Antenna feeds/WL_ANT1_J: C5204.1, J5202.1, R5202.2
/Audio/Audio: DAC left/DACL_DSDA: R2504.2, U2501.40
/Audio/Audio: DAC left/DACL_DSDCLK: R2505.2, U2501.32
/Audio/Audio: DAC left/DACL_FILTN: C2511.2, U2501.6
/Audio/Audio: DAC left/DACL_FILTP: C2509.2, U2501.5
/Audio/Audio: DAC left/DACL_FLYC_VCP: C2515.2, C2516.1, U2501.23
/Audio/Audio: DAC left/DACL_FLYN_VA: C2512.2, U2501.11
/Audio/Audio: DAC left/DACL_FLYN_VCP: C2516.2, U2501.20
/Audio/Audio: DAC left/DACL_FLYP_VA: C2512.1, U2501.10
/Audio/Audio: DAC left/DACL_FLYP_VCP: C2515.1, U2501.24
/Audio/Audio: DAC left/DACL_LRCK: R2503.2, U2501.38
/Audio/Audio: DAC left/DACL_NVA: C2510.1, C2511.1, U2501.9
/Audio/Audio: DAC left/DACL_SCLK: R2502.2, U2501.34
/Audio/Audio: DAC left/DACL_SDIN: R2501.2, U2501.2
/Audio/Audio: DAC left/DACL_VA_IN: C2501.1, R2506.2, TP2502.1, U2502.1
/Audio/Audio: DAC left/DACL_VCPF_N: C2514.1, U2501.18
/Audio/Audio: DAC left/DACL_VCPF_P: C2513.1, U2501.21
/Audio/Audio: DAC right/DACR_ADR: R2606.1, U2601.30
/Audio/Audio: DAC right/DACR_DSDA: R2604.2, U2601.40
/Audio/Audio: DAC right/DACR_DSDCLK: R2605.2, U2601.32
/Audio/Audio: DAC right/DACR_FILTN: C2611.2, U2601.6
/Audio/Audio: DAC right/DACR_FILTP: C2609.2, U2601.5
/Audio/Audio: DAC right/DACR_FLYC_VCP: C2615.2, C2616.1, U2601.23
/Audio/Audio: DAC right/DACR_FLYN_VA: C2612.2, U2601.11
/Audio/Audio: DAC right/DACR_FLYN_VCP: C2616.2, U2601.20
/Audio/Audio: DAC right/DACR_FLYP_VA: C2612.1, U2601.10
/Audio/Audio: DAC right/DACR_FLYP_VCP: C2615.1, U2601.24
/Audio/Audio: DAC right/DACR_LRCK: R2603.2, U2601.38
/Audio/Audio: DAC right/DACR_NVA: C2610.1, C2611.1, U2601.9
/Audio/Audio: DAC right/DACR_SCLK: R2602.2, U2601.34
/Audio/Audio: DAC right/DACR_SDIN: R2601.2, U2601.2
/Audio/Audio: DAC right/DACR_VA_IN: C2601.1, R2607.2, TP2602.1, U2602.1
/Audio/Audio: DAC right/DACR_VCPF_N: C2614.1, U2601.18
/Audio/Audio: DAC right/DACR_VCPF_P: C2613.1, U2601.21
/Audio/Audio: DAC supplies/AUDIO_2V2_SRC: C2304.1, L2301.2, R2303.1, TP2303.1, U2303.8
/Audio/Audio: DAC supplies/AUDIO_SW: L2301.1, U2303.7
/Audio/Audio: DAC supplies/AUDIO_VSET: R2302.1, U2303.5
/Audio/Audio: DAC supplies/DAC_DIG_1V8_SRC: R2301.1, TP2301.1, U2302.A1
/Audio/Audio: amplifier rails/Amplifier rails: +-6 V LDOs/HPA_N6_A: C2914.1, C2915.1, C2916.1, NT2903.1, U2903.10, U2903.11, U2903.12
/Audio/Audio: amplifier rails/Amplifier rails: +-6 V LDOs/HPA_N6_A_ILIM: R2905.1, U2903.6
/Audio/Audio: amplifier rails/Amplifier rails: +-6 V LDOs/HPA_N6_B: C2920.1, C2921.1, C2922.1, NT2904.1, U2904.10, U2904.11, U2904.12
/Audio/Audio: amplifier rails/Amplifier rails: +-6 V LDOs/HPA_N6_B_ILIM: R2906.1, U2904.6
/Audio/Audio: amplifier rails/Amplifier rails: +-6 V LDOs/HPA_N6_SET: C2923.1, C2924.1, R2907.1, R2908.1, U2903.8, U2904.8
/Audio/Audio: amplifier rails/Amplifier rails: +-6 V LDOs/HPA_P6_A: C2902.1, C2903.1, C2904.1, NT2901.1, U2901.9, U2901.10
/Audio/Audio: amplifier rails/Amplifier rails: +-6 V LDOs/HPA_P6_A_ILIM: R2901.1, U2901.5
/Audio/Audio: amplifier rails/Amplifier rails: +-6 V LDOs/HPA_P6_B: C2906.1, C2907.1, C2908.1, NT2902.1, U2902.9, U2902.10
/Audio/Audio: amplifier rails/Amplifier rails: +-6 V LDOs/HPA_P6_B_ILIM: R2902.1, U2902.5
/Audio/Audio: amplifier rails/Amplifier rails: +-6 V LDOs/HPA_P6_SET: C2909.1, C2910.1, R2903.1, R2904.1, U2901.7, U2902.7
/Audio/Audio: amplifier rails/Amplifier rails: +-7 V pre-rails/HPA_BOOST_CP: C2802.1, U2801.21
/Audio/Audio: amplifier rails/Amplifier rails: +-7 V pre-rails/HPA_BOOST_FB: C2801.2, R2802.2, R2803.1, U2801.22
/Audio/Audio: amplifier rails/Amplifier rails: +-7 V pre-rails/HPA_BOOST_SW: D2801.2, L2801.2, U2801.1, U2801.24
/Audio/Audio: amplifier rails/Amplifier rails: +-7 V pre-rails/HPA_BOOST_VIN: C2804.1, R2801.2, U2801.4, U2801.9
/Audio/Audio: amplifier rails/Amplifier rails: +-7 V pre-rails/HPA_BOOST_VREF: C2803.1, U2801.17
/Audio/Audio: amplifier rails/Amplifier rails: +-7 V pre-rails/HPA_N7_BOOT: C2812.1, U2802.4
/Audio/Audio: amplifier rails/Amplifier rails: +-7 V pre-rails/HPA_N7_EN: R2807.2, R2808.1, U2802.9
/Audio/Audio: amplifier rails/Amplifier rails: +-7 V pre-rails/HPA_N7_FB: C2811.1, R2804.2, R2805.1, U2802.7
/Audio/Audio: amplifier rails/Amplifier rails: +-7 V pre-rails/HPA_N7_LS_D: Q2802.2, R2807.1
/Audio/Audio: amplifier rails/Amplifier rails: +-7 V pre-rails/HPA_N7_LS_G: Q2801.3, Q2802.1, R2806.2
/Audio/Audio: amplifier rails/Amplifier rails: +-7 V pre-rails/HPA_N7_SW: C2812.2, L2802.1, U2802.12
/Audio/Audio: amplifier rails/Amplifier rails: +-7 V pre-rails/HPA_N7_VCC: C2813.1, U2802.5
/Audio/Audio: balanced output stage/Balanced output stage: left channel/HPB_LN_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: C3208.1, R3213.2, R3214.1, U3202.10
/Audio/Audio: balanced output stage/Balanced output stage: left channel/HPB_LN_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: C3210.1, R3217.2, R3218.1, U3202.6
/Audio/Audio: balanced output stage/Balanced output stage: left channel/HPB_LN_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: C3208.2, R3214.2, R3219.1, U3202.9
/Audio/Audio: balanced output stage/Balanced output stage: left channel/HPB_LN_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: C3210.2, R3218.2, R3220.1, U3202.7
/Audio/Audio: balanced output stage/Balanced output stage: left channel/HPB_LN_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: C3207.1, R3211.2, R3212.1, U3202.1
/Audio/Audio: balanced output stage/Balanced output stage: left channel/HPB_LN_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: C3209.1, R3215.2, R3216.1, U3202.5
/Audio/Audio: balanced output stage/Balanced output stage: left channel/HPB_LP_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: C3202.1, R3203.2, R3204.1, U3201.10
/Audio/Audio: balanced output stage/Balanced output stage: left channel/HPB_LP_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: C3204.1, R3207.2, R3208.1, U3201.6
/Audio/Audio: balanced output stage/Balanced output stage: left channel/HPB_LP_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: C3202.2, R3204.2, R3209.1, U3201.9
/Audio/Audio: balanced output stage/Balanced output stage: left channel/HPB_LP_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: C3204.2, R3208.2, R3210.1, U3201.7
/Audio/Audio: balanced output stage/Balanced output stage: left channel/HPB_LP_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: C3201.1, R3201.2, R3202.1, U3201.1
/Audio/Audio: balanced output stage/Balanced output stage: left channel/HPB_LP_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: C3203.1, R3205.2, R3206.1, U3201.5
/Audio/Audio: balanced output stage/Balanced output stage: right channel/HPB_RN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: C3308.1, R3313.2, R3314.1, U3302.10
/Audio/Audio: balanced output stage/Balanced output stage: right channel/HPB_RN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: C3310.1, R3317.2, R3318.1, U3302.6
/Audio/Audio: balanced output stage/Balanced output stage: right channel/HPB_RN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: C3308.2, R3314.2, R3319.1, U3302.9
/Audio/Audio: balanced output stage/Balanced output stage: right channel/HPB_RN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: C3310.2, R3318.2, R3320.1, U3302.7
/Audio/Audio: balanced output stage/Balanced output stage: right channel/HPB_RN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: C3307.1, R3311.2, R3312.1, U3302.1
/Audio/Audio: balanced output stage/Balanced output stage: right channel/HPB_RN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: C3309.1, R3315.2, R3316.1, U3302.5
/Audio/Audio: balanced output stage/Balanced output stage: right channel/HPB_RP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: C3302.1, R3303.2, R3304.1, U3301.10
/Audio/Audio: balanced output stage/Balanced output stage: right channel/HPB_RP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: C3304.1, R3307.2, R3308.1, U3301.6
/Audio/Audio: balanced output stage/Balanced output stage: right channel/HPB_RP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: C3302.2, R3304.2, R3309.1, U3301.9
/Audio/Audio: balanced output stage/Balanced output stage: right channel/HPB_RP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: C3304.2, R3308.2, R3310.1, U3301.7
/Audio/Audio: balanced output stage/Balanced output stage: right channel/HPB_RP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: C3301.1, R3301.2, R3302.1, U3301.1
/Audio/Audio: balanced output stage/Balanced output stage: right channel/HPB_RP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: C3303.1, R3305.2, R3306.1, U3301.5
/Audio/Audio: balanced output stage/HPA_N6V0_BAL: C3206.1, C3212.1, C3306.1, C3312.1, R3102.2, TP3104.1, U3201.4, U3201.11, U3202.4, U3202.11, U3301.4, U3301.11, U3302.4, U3302.11
/Audio/Audio: balanced output stage/HPA_P6V0_BAL: C3205.1, C3211.1, C3305.1, C3311.1, R3101.2, TP3102.1, U3201.2, U3202.2, U3301.2, U3302.2
/Audio/Audio: master clocks/DIVL_QN: U2404.2, U2404.3
/Audio/Audio: master clocks/DIVR_QN: U2405.2, U2405.3
/Audio/Audio: master clocks/MCLK1V8_IN: C2404.1, R2402.2, TP2404.1, U2403.1
/Audio/Audio: master clocks/MCLK3V1_IN: C2402.1, R2401.2, TP2402.1, U2402.1
/Audio/Audio: master clocks/MCLK_3V1_EN: U2401.4, U2402.3
/Audio/Audio: master clocks/MCLK_OSC: R2404.2, R2406.2, R2409.1, U2404.1, U2405.1
/Audio/Audio: single-ended output stage/HPA_N6V0_SE: C3006.1, C3012.1, R3022.2, TP3004.1, U3001.4, U3001.11, U3002.4, U3002.11
/Audio/Audio: single-ended output stage/HPA_P6V0_SE: C3005.1, C3011.1, R3021.2, TP3002.1, U3001.2, U3002.2
/Audio/Audio: single-ended output stage/HPS_L_NA: C3002.1, R3003.2, R3004.1, U3001.10
/Audio/Audio: single-ended output stage/HPS_L_NB: C3004.1, R3007.2, R3008.1, U3001.6
/Audio/Audio: single-ended output stage/HPS_L_OA: C3002.2, R3004.2, R3009.1, U3001.9
/Audio/Audio: single-ended output stage/HPS_L_OB: C3004.2, R3008.2, R3010.1, U3001.7
/Audio/Audio: single-ended output stage/HPS_L_PA: C3001.1, R3001.2, R3002.1, U3001.1
/Audio/Audio: single-ended output stage/HPS_L_PB: C3003.1, R3005.2, R3006.1, U3001.5
/Audio/Audio: single-ended output stage/HPS_R_NA: C3008.1, R3013.2, R3014.1, U3002.10
/Audio/Audio: single-ended output stage/HPS_R_NB: C3010.1, R3017.2, R3018.1, U3002.6
/Audio/Audio: single-ended output stage/HPS_R_OA: C3008.2, R3014.2, R3019.1, U3002.9
/Audio/Audio: single-ended output stage/HPS_R_OB: C3010.2, R3018.2, R3020.1, U3002.7
/Audio/Audio: single-ended output stage/HPS_R_PA: C3007.1, R3011.2, R3012.1, U3002.1
/Audio/Audio: single-ended output stage/HPS_R_PB: C3009.1, R3015.2, R3016.1, U3002.5
/Audio/DACL_AOUT_N: R3003.1, R3007.1, R3203.1, R3207.1, R3211.1, R3215.1, U2501.16
/Audio/DACL_AOUT_P: R3001.1, R3005.1, R3201.1, R3205.1, R3213.1, R3217.1, U2501.14
/Audio/DACR_AOUT_N: R3013.1, R3017.1, R3303.1, R3307.1, R3311.1, R3315.1, U2601.16
/Audio/DACR_AOUT_P: R3011.1, R3015.1, R3301.1, R3305.1, R3313.1, R3317.1, U2601.14
/Audio/MCLK_L: R2411.2, TP2503.1, U2501.37
/Audio/MCLK_R: R2412.2, TP2603.1, U2601.37
/BAT_F: F701.1, Q701.5, Q701.6, Q701.7, Q701.8, R701.1, R802.1
/BAT_MID: D702.2, J703.1, R801.1
/BL_LEDA: C5403.1, D5401.1, J5301.46
/BL_LEDK: J5301.45, R5401.1, U5401.1
/BL_PWM: U1301.AP7, U5401.5
/BT_UART_CTS: U1301.F37, U5001.50
/BT_UART_RTS: U1301.G37, U5001.52
/BT_UART_RXD: U1301.F38, U5001.51
/BT_UART_TXD: U1301.1C20, U5001.49
/BT_WAKE_IN: U1301.D37, U5001.75
/BT_WAKE_OUT: U1301.1T18, U5001.76
/CHG_INT_N: R1314.2, U601.21, U1301.AN38
/CLK32K_PMIC: R1311.2, U1101.68, U1301.1T20
/COVER_DET_N: D5801.2, R5801.2, TP5801.1, U1301.AJ38
/CPU core supply/VDD_CPU_CC: C1206.1, R1202.2
/CPU core supply/VDD_CPU_COMP: C1207.1, R1202.1, U1201.1
/CPU core supply/VDD_CPU_EN: C1205.1, R1201.2, U1201.4
/CPU core supply/VDD_CPU_GOS: C1206.2, C1207.2, NT1202.1, U1201.2
/CPU core supply/VDD_CPU_PG: R1204.2, TP1203.1, U1201.10
/CPU core supply/VDD_CPU_SRC: C1208.1, L1201.2, R1203.1, TP1201.1
/CPU core supply/VDD_CPU_SW: L1201.1, U1201.7
/CPU core supply/VDD_CPU_VOS: NT1201.1, TP1204.1, U1201.3
/Charger and battery path/BAT_NTC: D703.2, J704.1, R603.2, R604.1, U601.16
/Charger and battery path/CHG_BATP: C604.1, R701.2, U601.18
/Charger and battery path/CHG_SDRV: Q701.4, U601.24
/Charger and battery path/Charger: BQ25798/CHG1_SW: C602.2, L601.1, U601.28
/Charger and battery path/Charger: BQ25798/CHG2_SW: C603.2, L601.2, U601.26
/Charger and battery path/Charger: BQ25798/CHG_BTST1: C602.1, U601.4
/Charger and battery path/Charger: BQ25798/CHG_BTST2: C603.1, U601.19
/Charger and battery path/Charger: BQ25798/CHG_CE: R602.1, U601.13
/Charger and battery path/Charger: BQ25798/CHG_PMID: C608.1, C609.1, C610.1, C611.1, U601.29
/Charger and battery path/Charger: BQ25798/CHG_PROG: R601.1, U601.20
/Charger and battery path/Charger: BQ25798/CHG_QON: TP603.1, U601.12
/Charger and battery path/Charger: BQ25798/CHG_REGN: C601.1, R603.1, R605.1, U601.5, U601.17
/Charger and battery path/Charger: BQ25798/CHG_STAT: R605.2, TP602.1, U601.1
/Charger and battery path/Charger: battery path/BAT_P: D701.2, F701.2, J701.1, J702.1, TP702.1
/Charger and battery path/Charger: input mux/MUX_ILM: R507.1, U501.10
/Charger and battery path/Charger: input mux/MUX_OV1: D501.1, R501.2, R502.1, U501.5
/Charger and battery path/Charger: input mux/MUX_OV2: D502.1, R503.2, R504.1, U501.4
/Charger and battery path/Charger: input mux/MUX_PR1: R505.2, R506.1, U501.6
/Charger and battery path/Charger: input mux/MUX_SS: C501.1, U501.11
/Charger and battery path/Charger: input mux/MUX_ST: TP504.1, U501.9
/Coprocessor/Coprocessor: RP2354A/RP_BOOTSEL_D: Q3501.3, R3509.2
/Coprocessor/Coprocessor: RP2354A/RP_QSPI_SS: R3509.1, TP3504.1, U3501.60
/Coprocessor/Coprocessor: RP2354A/RP_SPARE: TP3505.1, U3501.5
/Coprocessor/Coprocessor: RP2354A/RP_TAP_BCLK: R3504.2, U3501.7
/Coprocessor/Coprocessor: RP2354A/RP_TAP_DSD_L: R3507.2, U3501.10
/Coprocessor/Coprocessor: RP2354A/RP_TAP_DSD_R: R3508.2, U3501.12
/Coprocessor/Coprocessor: RP2354A/RP_TAP_LRCK: R3505.2, U3501.8
/Coprocessor/Coprocessor: RP2354A/RP_TAP_SDO0: R3506.2, U3501.9
/Coprocessor/Coprocessor: RP2354A/RP_USB_DM_R: R3503.2, U3501.51
/Coprocessor/Coprocessor: RP2354A/RP_USB_DP_R: R3502.2, U3501.52
/Coprocessor/Coprocessor: RP2354A/RP_XIN: U3501.21, Y3501.3
/Coprocessor/Coprocessor: supplies/RP_3V3_SRC: R3511.1, TP3506.1, U3502.A1
/Coprocessor/Coprocessor: supplies/RP_DVDD: C3512.1, C3513.1, C3514.1, L3501.2, U3501.6, U3501.23, U3501.39, U3501.50
/Coprocessor/Coprocessor: supplies/RP_IOVDD_1V8_SRC: R3512.1, TP3508.1, U3503.A1
/Coprocessor/Coprocessor: supplies/RP_VREG_AVDD: C3515.1, R3510.2, U3501.46
/Coprocessor/Coprocessor: supplies/RP_VREG_SW: L3501.1, U3501.48
/DAC_DIG_EN: R1329.1, U1301.AF2, U2302.B2
/DAC_I2C_SCL: R1322.2, R1323.2, U1302.2, U2501.1, U2601.1
/DAC_I2C_SDA: R1324.2, R1325.2, U1302.6, U2501.39, U2601.39
/DAC_INT_N: R1326.2, U1301.AJ2, U2501.27, U2601.27
/DAC_RST_N: R1327.1, U1301.1R1, U2501.28, U2601.28
/DAC_VP_EN: R1328.1, U1301.AE2, U2301.B2
/DBG_UART_RX: TP4302.1, U1301.1V19
/DBG_UART_TX: TP4301.1, U1301.1U18
/DSD_L: R2504.1, R3507.1, TP4307.1, U1301.1L2
/DSD_R: R2604.1, R3508.1, TP4308.1, U1301.AG2
/EFUSE_5V_FLT_N: R6708.2, U4501.4, U6701.16
/EFUSE_HAT5V_FLT_N: R6707.2, U4801.4, U6701.15
/EFUSE_HAT5V_IMON: C1306.1, C4803.1, R4802.2, U1301.1B18
/EFUSE_VBUS_FLT_N: R6709.2, U4502.4, U6701.17
/EFUSE_VBUS_IMON: C1307.1, C4505.1, R4503.2, U1301.1A19
/EMMC_CLK: R3801.1, U1301.A29
/EMMC_CMD: R3802.2, U1301.A27, U3801.M5
/EMMC_D0: R3803.2, R4106.2, U1301.A32, U3801.A3
/EMMC_D1: U1301.B27, U3801.A4
/EMMC_D2: U1301.B32, U3801.A5
/EMMC_D3: U1301.B29, U3801.B2
/EMMC_D4: U1301.B33, U3801.B3
/EMMC_D5: U1301.A30, U3801.B4
/EMMC_D6: U1301.B30, U3801.B5
/EMMC_D7: U1301.A33, U3801.B6
/EMMC_DS: R3804.1, U1301.1A16, U3801.H5
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

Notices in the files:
board/hardware/t1-main-board/t1-main-board.kicad_pcb:
CERN-OHL-S-2.0
